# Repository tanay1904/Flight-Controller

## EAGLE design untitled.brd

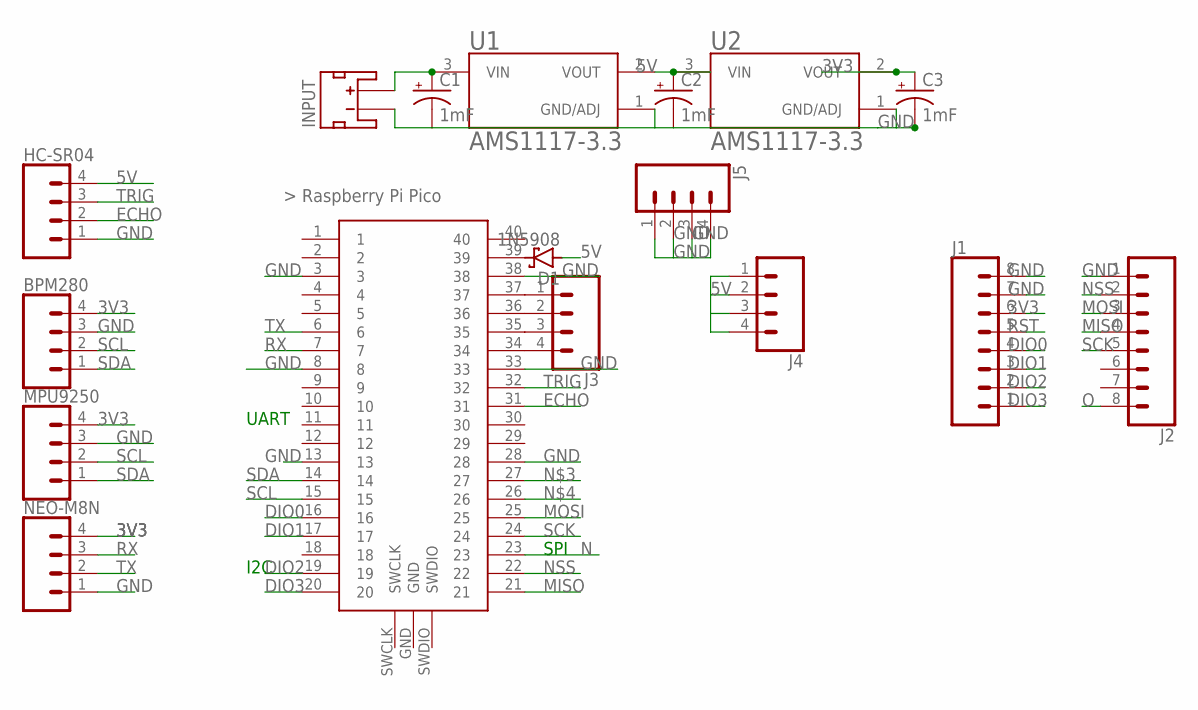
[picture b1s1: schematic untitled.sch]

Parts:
BPM280: CONN_04PTH; 1X04
C1, C2, C3: 1mF; CPOL-RADIAL-5MM-10MM
D1: 1N5908; C4111-15
HC-SR04: CONN_04PTH; 1X04
INPUT: JST_2MM_MALE; JST-2-SMD
J1, J2: CONN_08NO_SILK_DNP; 1X08_NO_SILK
J3, J4, J5: CONN_041X04_NO_SILK; 1X04_NO_SILK
MPU9250: CONN_04PTH; 1X04
NEO-M8N: CONN_04PTH; 1X04
U1, U2: AMS1117-3.3; SOT229P700X180-4N
U$1: RASPBERRY-PI-PICO_TH; FT_RASPBERRY-PI-PICO_TH

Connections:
3V3: BPM280.4, C3.+, J1.6, MPU9250.4, NEO-M8N.4, U2.2 (VOUT)
5V: C2.+, D1.A, HC-SR04.4, J4.1, J4.2, J4.3, J4.4, U1.2 (VOUT), U2.3 (VIN)
DIO0: J1.4, U$1.16
DIO1: J1.3, U$1.17
DIO2: J1.2, U$1.19
DIO3: J1.1, U$1.20
ECHO: HC-SR04.2, U$1.31
GND: BPM280.3, C1.-, C2.-, C3.-, HC-SR04.1, INPUT.1 (-), J1.7, J1.8, J2.1, J5.1, J5.2, J5.3, J5.4, MPU9250.3, NEO-M8N.1, U1.1 (GND/ADJ), U2.1 (GND/ADJ), U$1.3, U$1.8, U$1.13, U$1.28, U$1.33, U$1.38
MISO: J2.4, U$1.21
MOSI: J2.3, U$1.25
N: U$1.23
unnamed: C1.+, INPUT.2 (+), U1.3 (VIN)
unnamed: D1.C, U$1.39
unnamed: J3.1, U$1.37
unnamed: J3.2, U$1.36
unnamed: J3.3, U$1.35
unnamed: J3.4, U$1.34
NSS: J2.2, U$1.22
O: J2.8
RST: J1.5
RX: NEO-M8N.3, U$1.7
SCK: J2.5, U$1.24
SCL: BPM280.2, MPU9250.2, U$1.15
SDA: BPM280.1, MPU9250.1, U$1.14
TRIG: HC-SR04.3, U$1.32
TX: NEO-M8N.2, U$1.6

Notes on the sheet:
SPI
I2C
UART

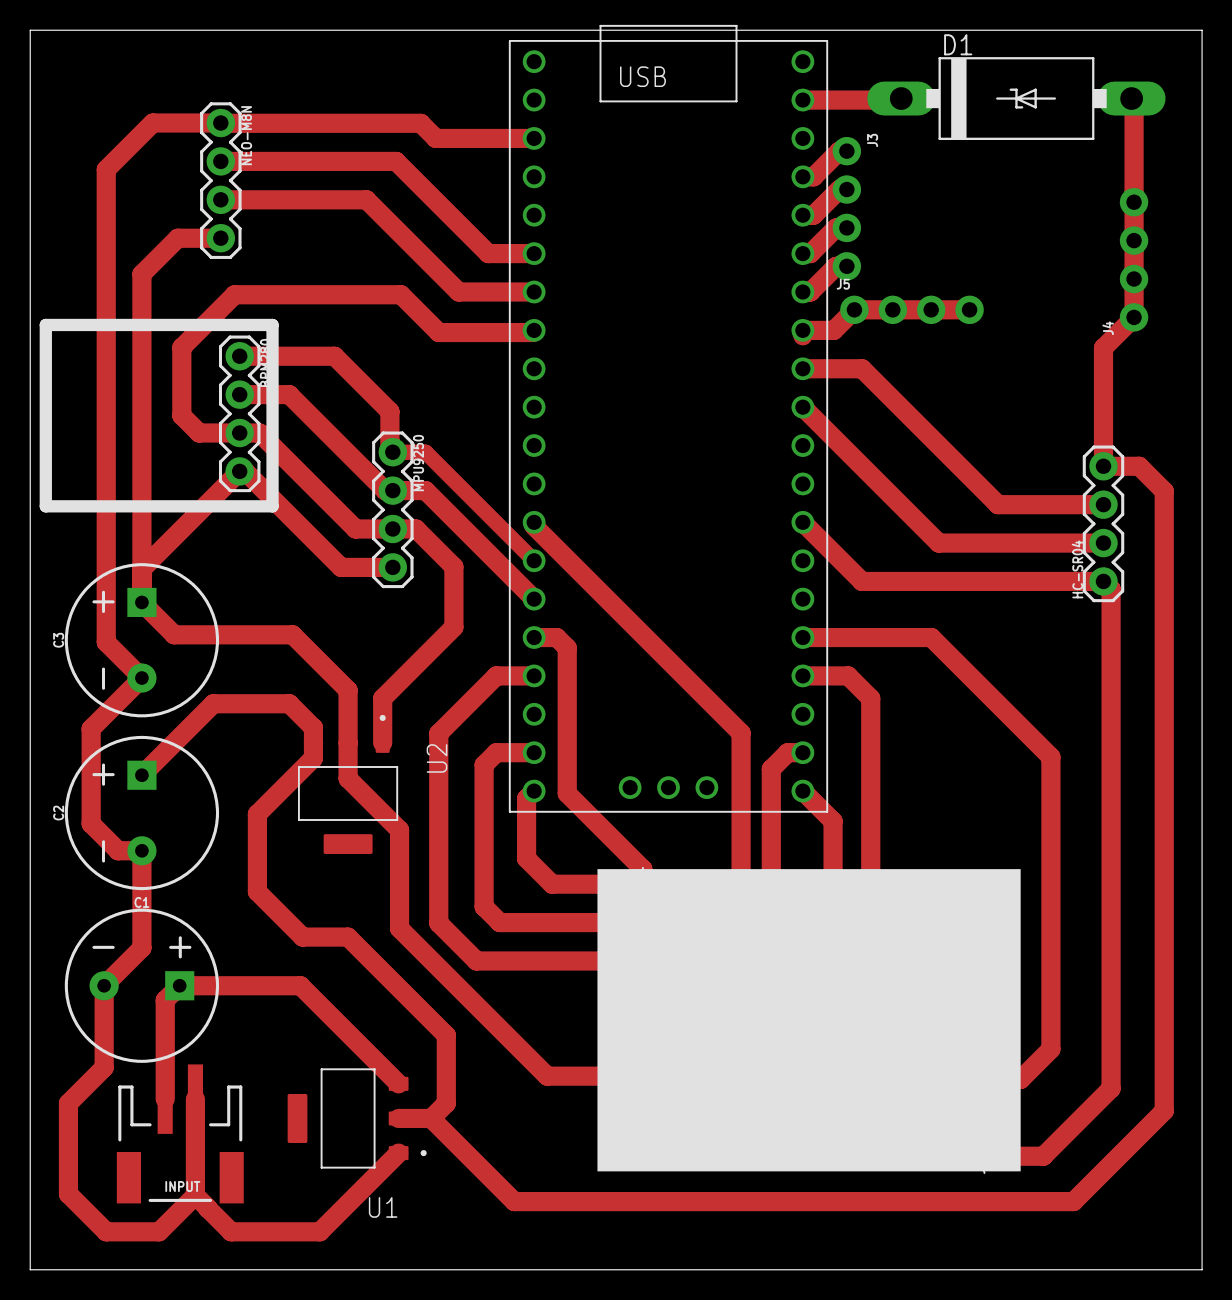
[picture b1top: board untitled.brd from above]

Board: 2 copper layers, 77.5 x 82.0 mm, 17 parts (0 on the bottom side), 23 nets.

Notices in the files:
parts and their libraries:
SparkFun-Connectors: Licensing: Creative Commons ShareAlike 4.0 International - https://creativecommons.org/licenses/by-sa/4.0
